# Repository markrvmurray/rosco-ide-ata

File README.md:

# IDE/ATA Interface for Rosco_68k

**(c) 2021 Mark R V Murray**

_v1.1 - first public release_

This is a minimalist PIO-only interface to PATA hard disk and
compatible devices.

It has received minimal testing, and is being released in the hope
that it may be useful to someone, somewhere.

The materials in this repository will, when assembled, give a board
that will map the IDE registers into the Rosco_68k's address space.

The addresses are mapped as follows:

| Address | Read | Write | Width in bits |
--- | --- | --- | ---
| 00F80040 | DATA | DATA | 16 |
| 00F80042 | Error | Features | 8 |
| 00F80044 | Sector Count | Sector Count | 8 |
| 00F80046 | Sector Number | Sector Number | 8 |
| 00F80048 | Cylinder Low | Cyllinder Low | 8 |
| 00F8004A | Cylinder High | Cylinder High | 8 |
| 00F8004C | Device and Head | Device and Head | 8 |
| 00F8004E | Status | Command | 8 |
| 00F80050 | (Not used) | | |
| 00F80052 | (Not used) | | |
| 00F80054 | (Not used) | | |
| 00F80056 | (Not used) | | |
| 00F80058 | (Not used) | | |
| 00F8005A | (Not used) | | |
| 00F8005C | Alternate Status | Device Control | 8 |
| 00F8005E | (Not used) | | |

The above memory locations base address may be changed by changing
the U1 image.  This is written in CUPL, and you will need a programmer
capable of programming GAL16V8s or the equivalent.

The supplied GAL images and jumper setting defaults will give the
IDE device IPL3. To change this, the three IPL jumpers on the board
will need to be changed; IPL0 and IPL1 can be cut, and all three
can be (re-)bridged with a solder blob if necessary.

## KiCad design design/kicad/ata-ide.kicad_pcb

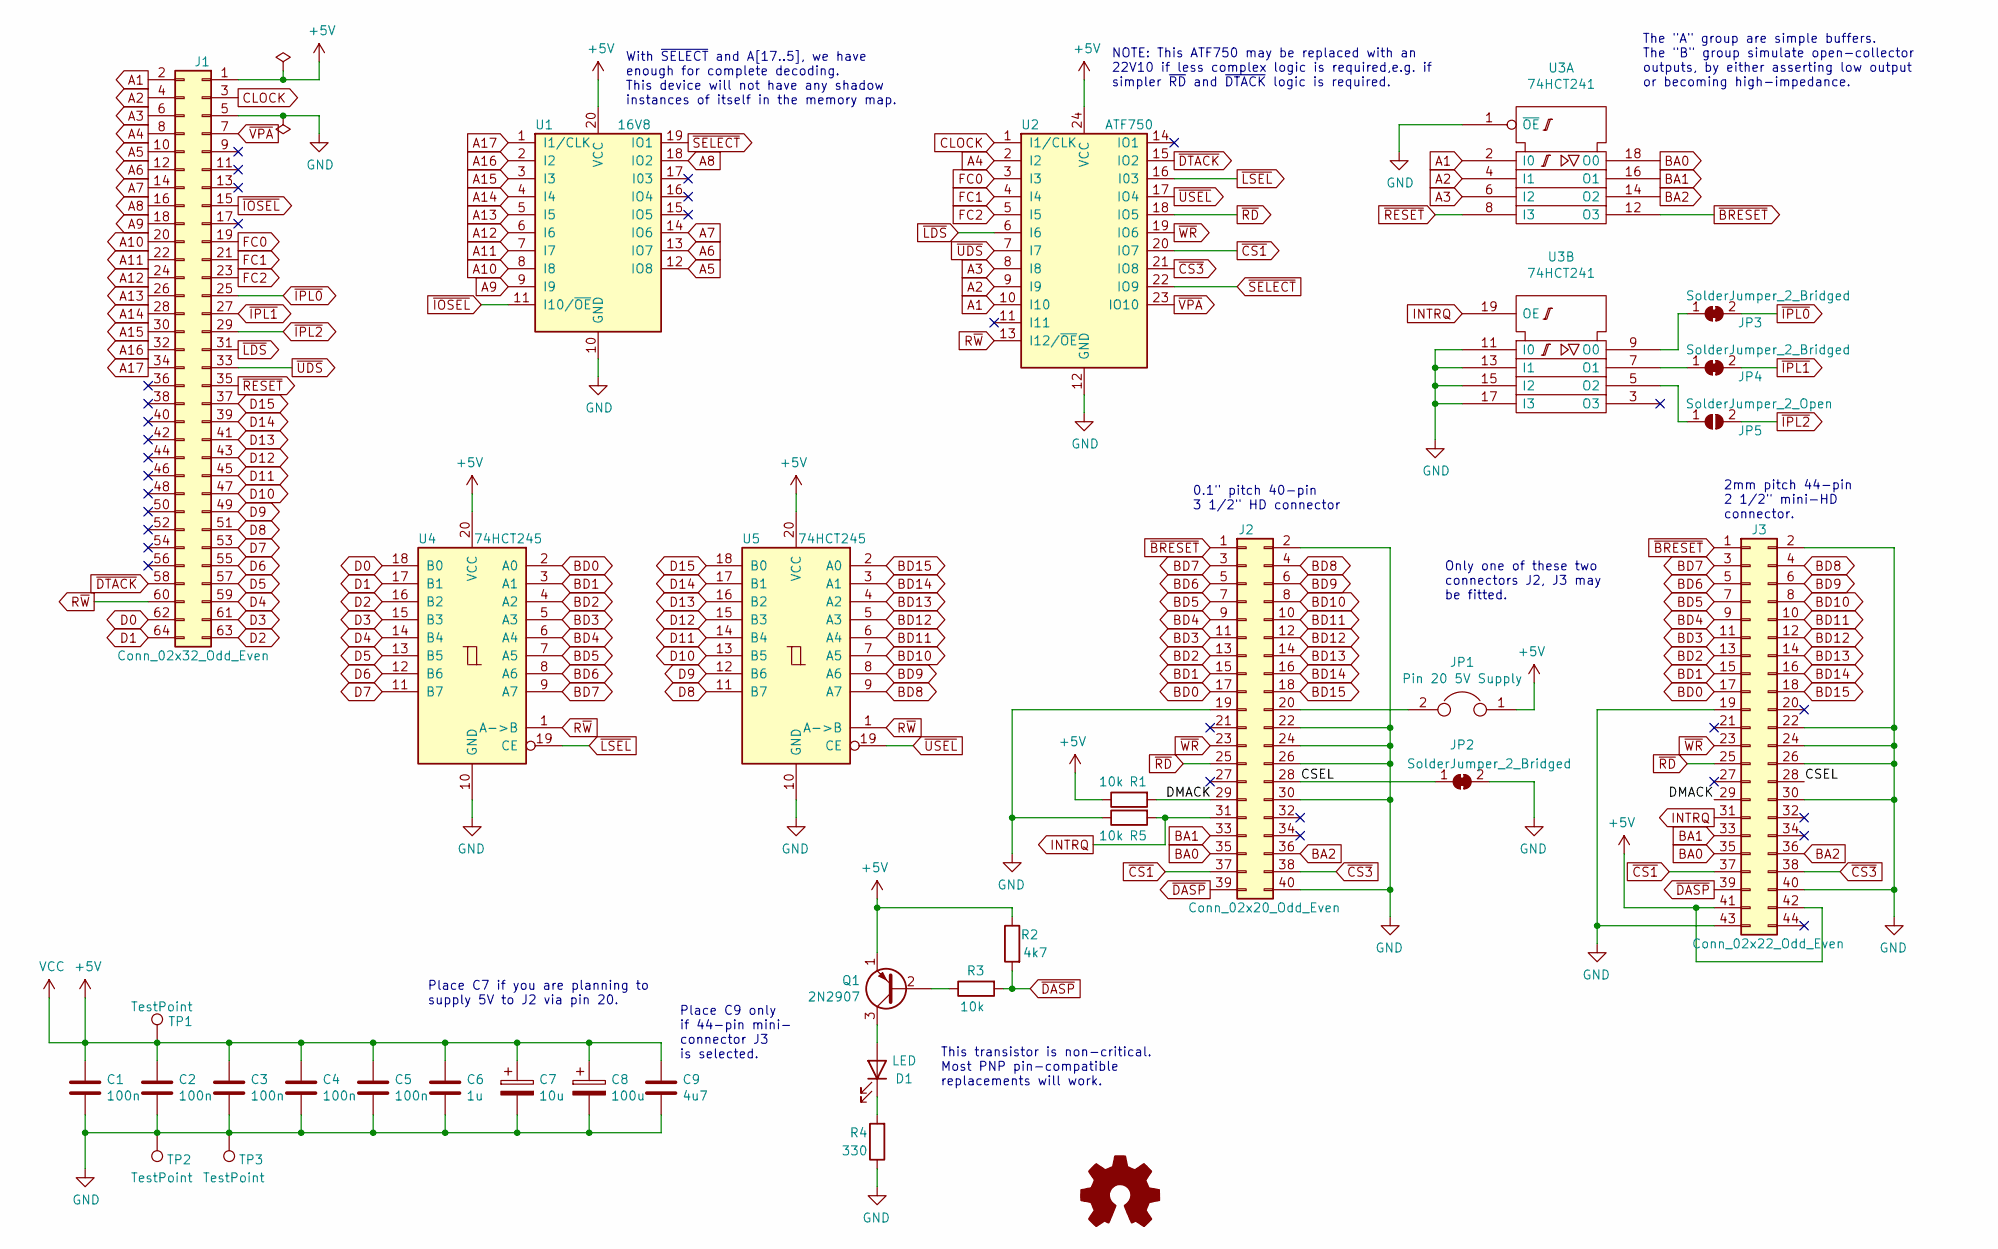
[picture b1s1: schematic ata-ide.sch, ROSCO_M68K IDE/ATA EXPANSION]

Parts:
C1, C2, C3, C4, C5: 100n; C_Rect_L4.0mm_W2.5mm_P2.50mm
C6: 1u; C_Rect_L7.0mm_W4.5mm_P5.00mm
C7: 10u; CP_Radial_D8.0mm_P2.50mm
C8: 100u; CP_Radial_D8.0mm_P2.50mm
C9: 4u7; C_Rect_L7.0mm_W4.5mm_P5.00mm
D1: LED; LED_D5.0mm
J1: Conn_02x32_Odd_Even; PinHeader_2x32_P2.54mm_Vertical
J2: Conn_02x20_Odd_Even; Pin_Header_Straight_2x20_Pitch2.54mm
J3: Conn_02x22_Odd_Even; Pin_Header_Straight_2x22_Pitch2.00mm
JP1: Pin 20 5V Supply; Pin_Header_Straight_1x02_Pitch2.54mm
JP2, JP3, JP4: SolderJumper_2_Bridged; SolderJumper-2_P1.3mm_Bridged_Pad1.0x1.5mm
JP5: SolderJumper_2_Open; SolderJumper-2_P1.3mm_Open_Pad1.0x1.5mm
Q1: 2N2907; TO-18-3
R1, R3, R5: 10k; R_Axial_DIN0207_L6.3mm_D2.5mm_P10.16mm_Horizontal
R2: 4k7; R_Axial_DIN0207_L6.3mm_D2.5mm_P10.16mm_Horizontal
R4: 330; R_Axial_DIN0207_L6.3mm_D2.5mm_P10.16mm_Horizontal
TP1, TP2, TP3: TestPoint; Measurement_Point_Round-TH_Big
U1: 16V8; DIP-20_W7.62mm_Socket_LongPads
U2: ATF750; DIP-24_W7.62mm_Socket_LongPads
U3: 74HCT241; DIP-20_W7.62mm_Socket_LongPads
U4, U5: 74HCT245; DIP-20_W7.62mm_Socket_LongPads

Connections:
/CSEL: J2.28, J3.28, JP2.1 (A)
/DMACK: J2.29, J3.29, R1.2
A1: J1.2, U2.10 (I10), U3.2 (I0)
A2: J1.4, U2.9 (I9), U3.4 (I1)
A3: J1.6, U2.8 (I8), U3.6 (I2)
A4: J1.8, U2.2 (I2)
A5: J1.10, U1.12 (IO8)
A6: J1.12, U1.13 (IO7)
A7: J1.14, U1.14 (IO6)
A8: J1.16, U1.18 (IO2)
A9: J1.18, U1.9 (I9)
A10: J1.20, U1.8 (I8)
A11: J1.22, U1.7 (I7)
A12: J1.24, U1.6 (I6)
A13: J1.26, U1.5 (I5)
A14: J1.28, U1.4 (I4)
A15: J1.30, U1.3 (I3)
A16: J1.32, U1.2 (I2)
A17: J1.34, U1.1 (I1/CLK)
BA0: J2.35, J3.35, U3.18 (O0)
BA1: J2.33, J3.33, U3.16 (O1)
BA2: J2.36, J3.36, U3.14 (O2)
BD0: J2.17, J3.17, U4.2 (A0)
BD1: J2.15, J3.15, U4.3 (A1)
BD2: J2.13, J3.13, U4.4 (A2)
BD3: J2.11, J3.11, U4.5 (A3)
BD4: J2.9, J3.9, U4.6 (A4)
BD5: J2.7, J3.7, U4.7 (A5)
BD6: J2.5, J3.5, U4.8 (A6)
BD7: J2.3, J3.3, U4.9 (A7)
BD8: J2.4, J3.4, U5.9 (A7)
BD9: J2.6, J3.6, U5.8 (A6)
BD10: J2.8, J3.8, U5.7 (A5)
BD11: J2.10, J3.10, U5.6 (A4)
BD12: J2.12, J3.12, U5.5 (A3)
BD13: J2.14, J3.14, U5.4 (A2)
BD14: J2.16, J3.16, U5.3 (A1)
BD15: J2.18, J3.18, U5.2 (A0)
CLOCK: J1.3, U2.1 (I1/CLK)
D0: J1.62, U4.18 (B0)
D1: J1.64, U4.17 (B1)
D2: J1.63, U4.16 (B2)
D3: J1.61, U4.15 (B3)
D4: J1.59, U4.14 (B4)
D5: J1.57, U4.13 (B5)
D6: J1.55, U4.12 (B6)
D7: J1.53, U4.11 (B7)
D8: J1.51, U5.11 (B7)
D9: J1.49, U5.12 (B6)
D10: J1.47, U5.13 (B5)
D11: J1.45, U5.14 (B4)
D12: J1.43, U5.15 (B3)
D13: J1.41, U5.16 (B2)
D14: J1.39, U5.17 (B1)
D15: J1.37, U5.18 (B0)
FC0: J1.19, U2.3 (I3)
FC1: J1.21, U2.4 (I4)
FC2: J1.23, U2.5 (I5)
INTRQ: J2.31, J3.31, R5.2, U3.19 (OE)
unnamed: D1.1 (K), R4.2
unnamed: D1.2 (A), Q1.3 (C)
unnamed: J2.20, JP1.2
unnamed: JP3.1 (A), U3.9 (O0)
unnamed: JP4.1 (A), U3.7 (O1)
unnamed: JP5.1 (A), U3.5 (O2)
unnamed: Q1.2 (B), R3.1
R~W~: J1.60, U2.13 (I12/~OE~), U4.1 (A->B), U5.1 (A->B)
~BRESET~: J2.1, J3.1, U3.12 (O3)
~CS1~: J2.37, J3.37, U2.20 (IO7)
~CS3~: J2.38, J3.38, U2.21 (IO8)
~DASP~: J2.39, J3.39, R2.2, R3.2
~DTACK~: J1.58, U2.15 (IO2)
~IOSEL~: J1.15, U1.11 (I10/~OE~)
~IPL0~: J1.25, JP3.2 (B)
~IPL1~: J1.27, JP4.2 (B)
~IPL2~: J1.29, JP5.2 (B)
~LDS~: J1.31, U2.6 (I6)
~LSEL~: U2.16 (I03), U4.19 (CE)
~RD~: J2.25, J3.25, U2.18 (IO5)
~RESET~: J1.35, U3.8 (I3)
~SELECT~: U1.19 (IO1), U2.22 (IO9)
~UDS~: J1.33, U2.7 (I7)
~USEL~: U2.17 (IO4), U5.19 (CE)
~VPA~: J1.7, U2.23 (IO10)
~WR~: J2.23, J3.23, U2.19 (IO6)

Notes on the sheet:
NOTE: This ATF750 may be replaced with an 22V10 if less complex logic is required,e.g. if simpler ~RD~ and ~DTACK~ logic is required.
The "A" group are simple buffers. The "B" group simulate open-collector outputs, by either asserting low output or becoming high-impedance.
With ~SELECT~ and A[17..5], we have enough for complete decoding. This device will not have any shadow instances of itself in the memory map.
This transistor is non-critical. Most PNP pin-compatible replacements will work.
Only one of these two connectors J2, J3 may be fitted.
Place C9 only if 44-pin mini- connector J3 is selected.
Place C7 if you are planning to supply 5V to J2 via pin 20.
0.1" pitch 40-pin 3 1/2" HD connector
2mm pitch 44-pin 2 1/2" mini-HD connector.

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
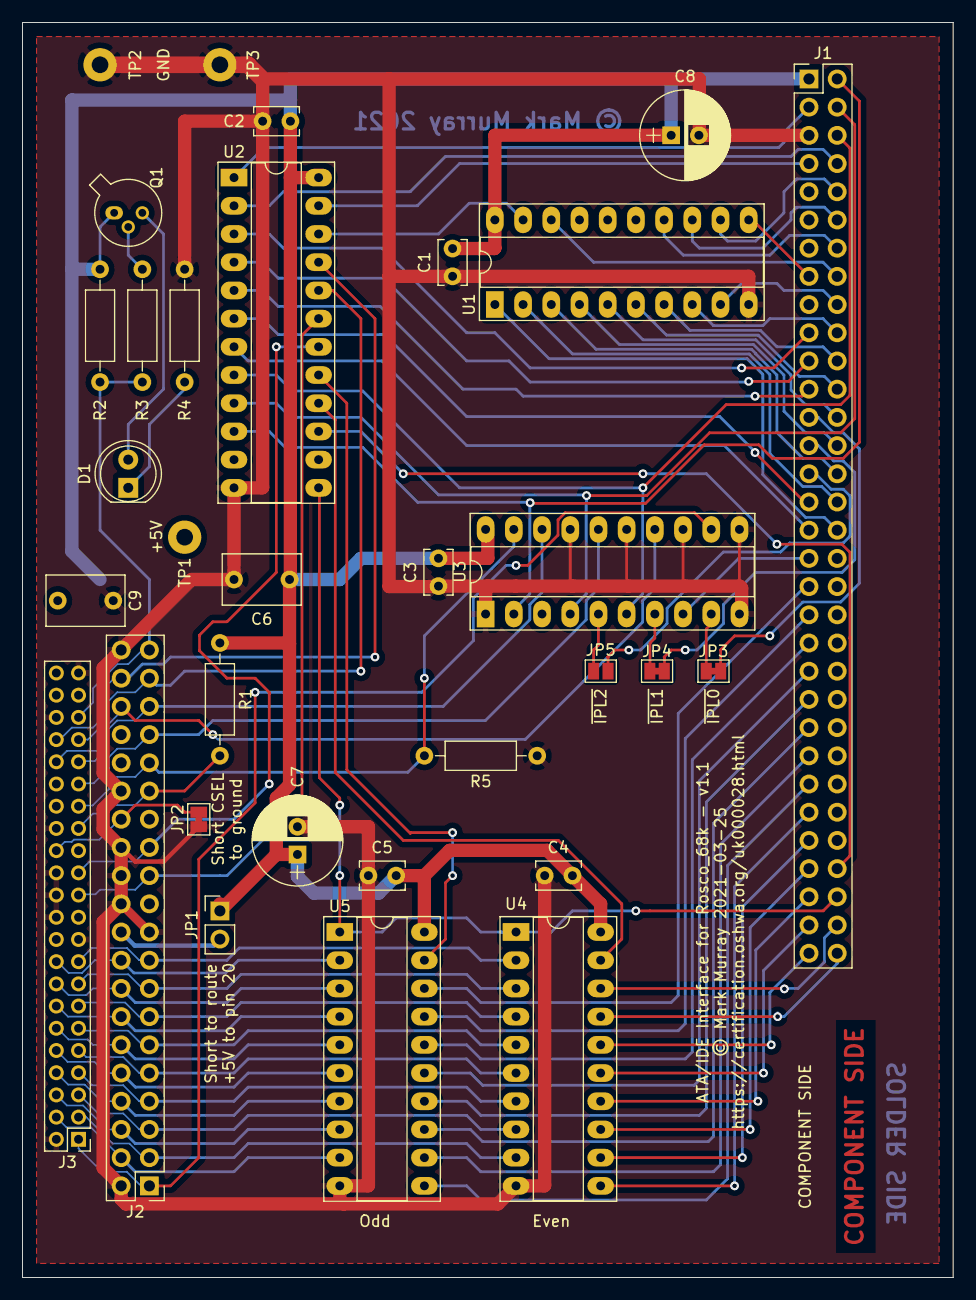
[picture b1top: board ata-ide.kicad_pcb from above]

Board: 2 copper layers, 83.8 x 113.0 mm, 32 parts (0 on the bottom side), 87 nets.

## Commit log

2021-03-21 Initial snapshot of v1.0
2021-03-21 Add line copped off in the rush.
2021-03-28 Update for version 1.1.
2021-03-28 Add much-needed .gitattributes to keep line-endings right.
2021-03-28 Correct address of device.
2021-03-28 Update to PDF of 1.1 schematic.
2021-04-05 Catch up rest of materials to 1.1.
2021-04-08 Make the status and error registor outputs a but more readable.
2021-04-10 PCB v1.1 RC1
2021-04-11 Improve readability of the C demo code.
2021-04-11 Add some tweeks to make things easier for builders.
2021-04-11 Add some comments and correct dates.

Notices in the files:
design/kicad/ata-ide.kicad_pcb:
Open Source Hardware licenced under CERN Open Hardware Licence
Copyright ©2021 Mark Murray
© Mark Murray 2021-03-25
